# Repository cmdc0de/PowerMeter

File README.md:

# PowerMeter
My take on the power meter inspired by GreatScott

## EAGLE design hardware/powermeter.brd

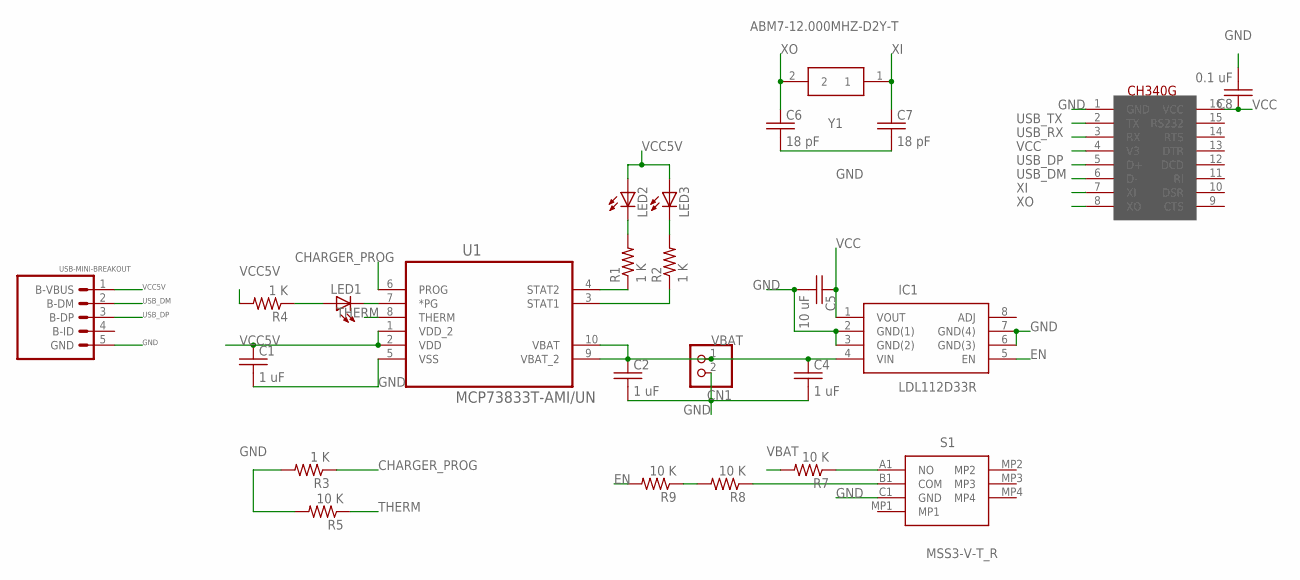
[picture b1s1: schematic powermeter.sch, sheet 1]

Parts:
C1, C2, C4: 1 uF; C0805K
C5: 10 uF; C0805K
C6, C7: 18 pF; C0805K
C8: 0.1 uF; C0805K
CN1: JST_2PIN-THM-RA; JST-PH-2-THM-RA
IC1: LDL112D33R; SOIC127P600X175-8N
LED1, LED2, LED3: LEDXZCFBB53W-8VF-2MA-LED; LEDC1606X95N
R1, R2, R3, R4: 1 K; R0805
R5, R7, R8, R9: 10 K; R0805
S1: MSS3-V-T_R; MSS3VTR
U1: MCP73833T-AMI/UN; SOP50P490X110-10N
U$4: CH340G; SOIC16
USB-MINI-BREAKOUT: USB-MINI-BREAKOUT; 1X05_LONGPADS
Y1: ABM7-12.000MHZ-D2Y-T; ABM7

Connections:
CHARGER_PROG: R3.1, U1.6 (PROG)
EN: IC1.5 (EN), R9.2
GND: C1.2, C2.2, C4.2, C5.2, C6.2, C7.2, C8.2, CN1.2 (1), IC1.2 (GND(1)), IC1.3 (GND(2)), IC1.6 (GND(3)), IC1.7 (GND(4)), R3.2, R5.2, S1.C1 (GND), U1.5 (VSS), U$4.1 (GND), USB-MINI-BREAKOUT.5 (GND); also elsewhere on the board
unnamed: R1.1, U1.4 (STAT2)
unnamed: LED1.2 (C), U1.7 (*PG)
unnamed: LED1.1 (A), R4.1
unnamed: LED3.2 (C), R2.2
unnamed: R2.1, U1.3 (STAT1)
unnamed: LED2.2 (C), R1.2
unnamed: R8.2, R9.1
unnamed: R8.1, S1.B1 (COM)
unnamed: R7.1, S1.A1 (NO)
THERM: R5.1, U1.8 (THERM)
USB_DM: U$4.6 (D-), USB-MINI-BREAKOUT.2 (B-DM)
USB_DP: U$4.5 (D+), USB-MINI-BREAKOUT.3 (B-DP)
USB_RX: U$4.3 (RX); also elsewhere on the board
USB_TX: U$4.2 (TX); also elsewhere on the board
VBAT: C2.1, C4.1, CN1.1 (2), IC1.4 (VIN), R7.2, U1.9 (VBAT_2), U1.10 (VBAT)
VCC: C5.1, C8.1, IC1.1 (VOUT), U$4.4 (V3), U$4.16 (VCC); also elsewhere on the board
VCC5V: C1.1, LED2.1 (A), LED3.1 (A), R4.2, U1.1 (VDD_2), U1.2 (VDD), USB-MINI-BREAKOUT.1 (B-VBUS); also elsewhere on the board
XI: C7.1, U$4.7 (XI), Y1.1
XO: C6.1, U$4.8 (XO), Y1.2

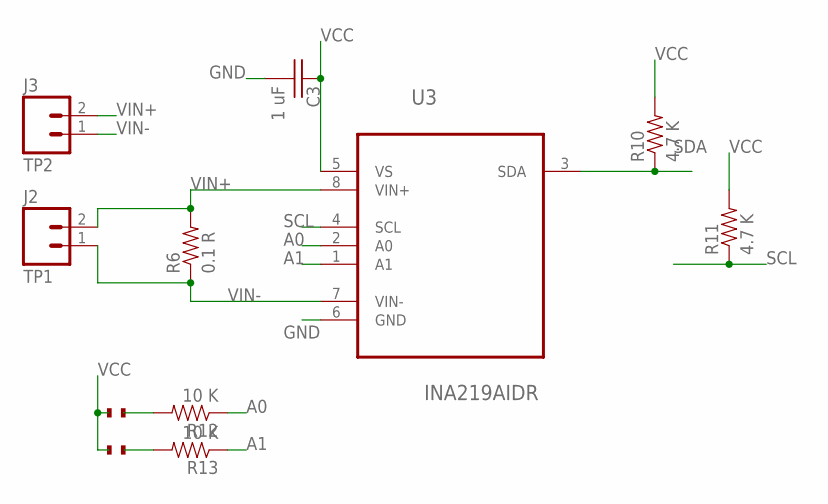
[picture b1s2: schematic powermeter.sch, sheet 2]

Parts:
C3: 1 uF; C0805K
J2: TP1; SCREWTERMINAL-3.5MM-2
J3: TP2; 1X02_LOCK_LONGPADS
R6: 0.1 R; R2010
R10, R11: 4.7 K; R0805
R12, R13: 10 K; R0805
U3: INA219AIDR; SOIC127P600X175-8N
U$1, U$2: SURFACE_MOUNT_JUMP; SURFACE_JUMPER

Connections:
A0: R12.1, U3.2 (A0)
A1: R13.1, U3.1 (A1)
GND: C3.2, U3.6 (GND); also elsewhere on the board
unnamed: R12.2, U$1.2
unnamed: R13.2, U$2.2
SCL: R11.1, U3.4 (SCL); also elsewhere on the board
SDA: R10.1, U3.3 (SDA); also elsewhere on the board
VCC: C3.1, R10.2, R11.2, U3.5 (VS), U$1.1, U$2.1; also elsewhere on the board
VIN+: J2.2, J3.2, R6.2, U3.8 (VIN+)
VIN-: J2.1, J3.1, R6.1, U3.7 (VIN-)

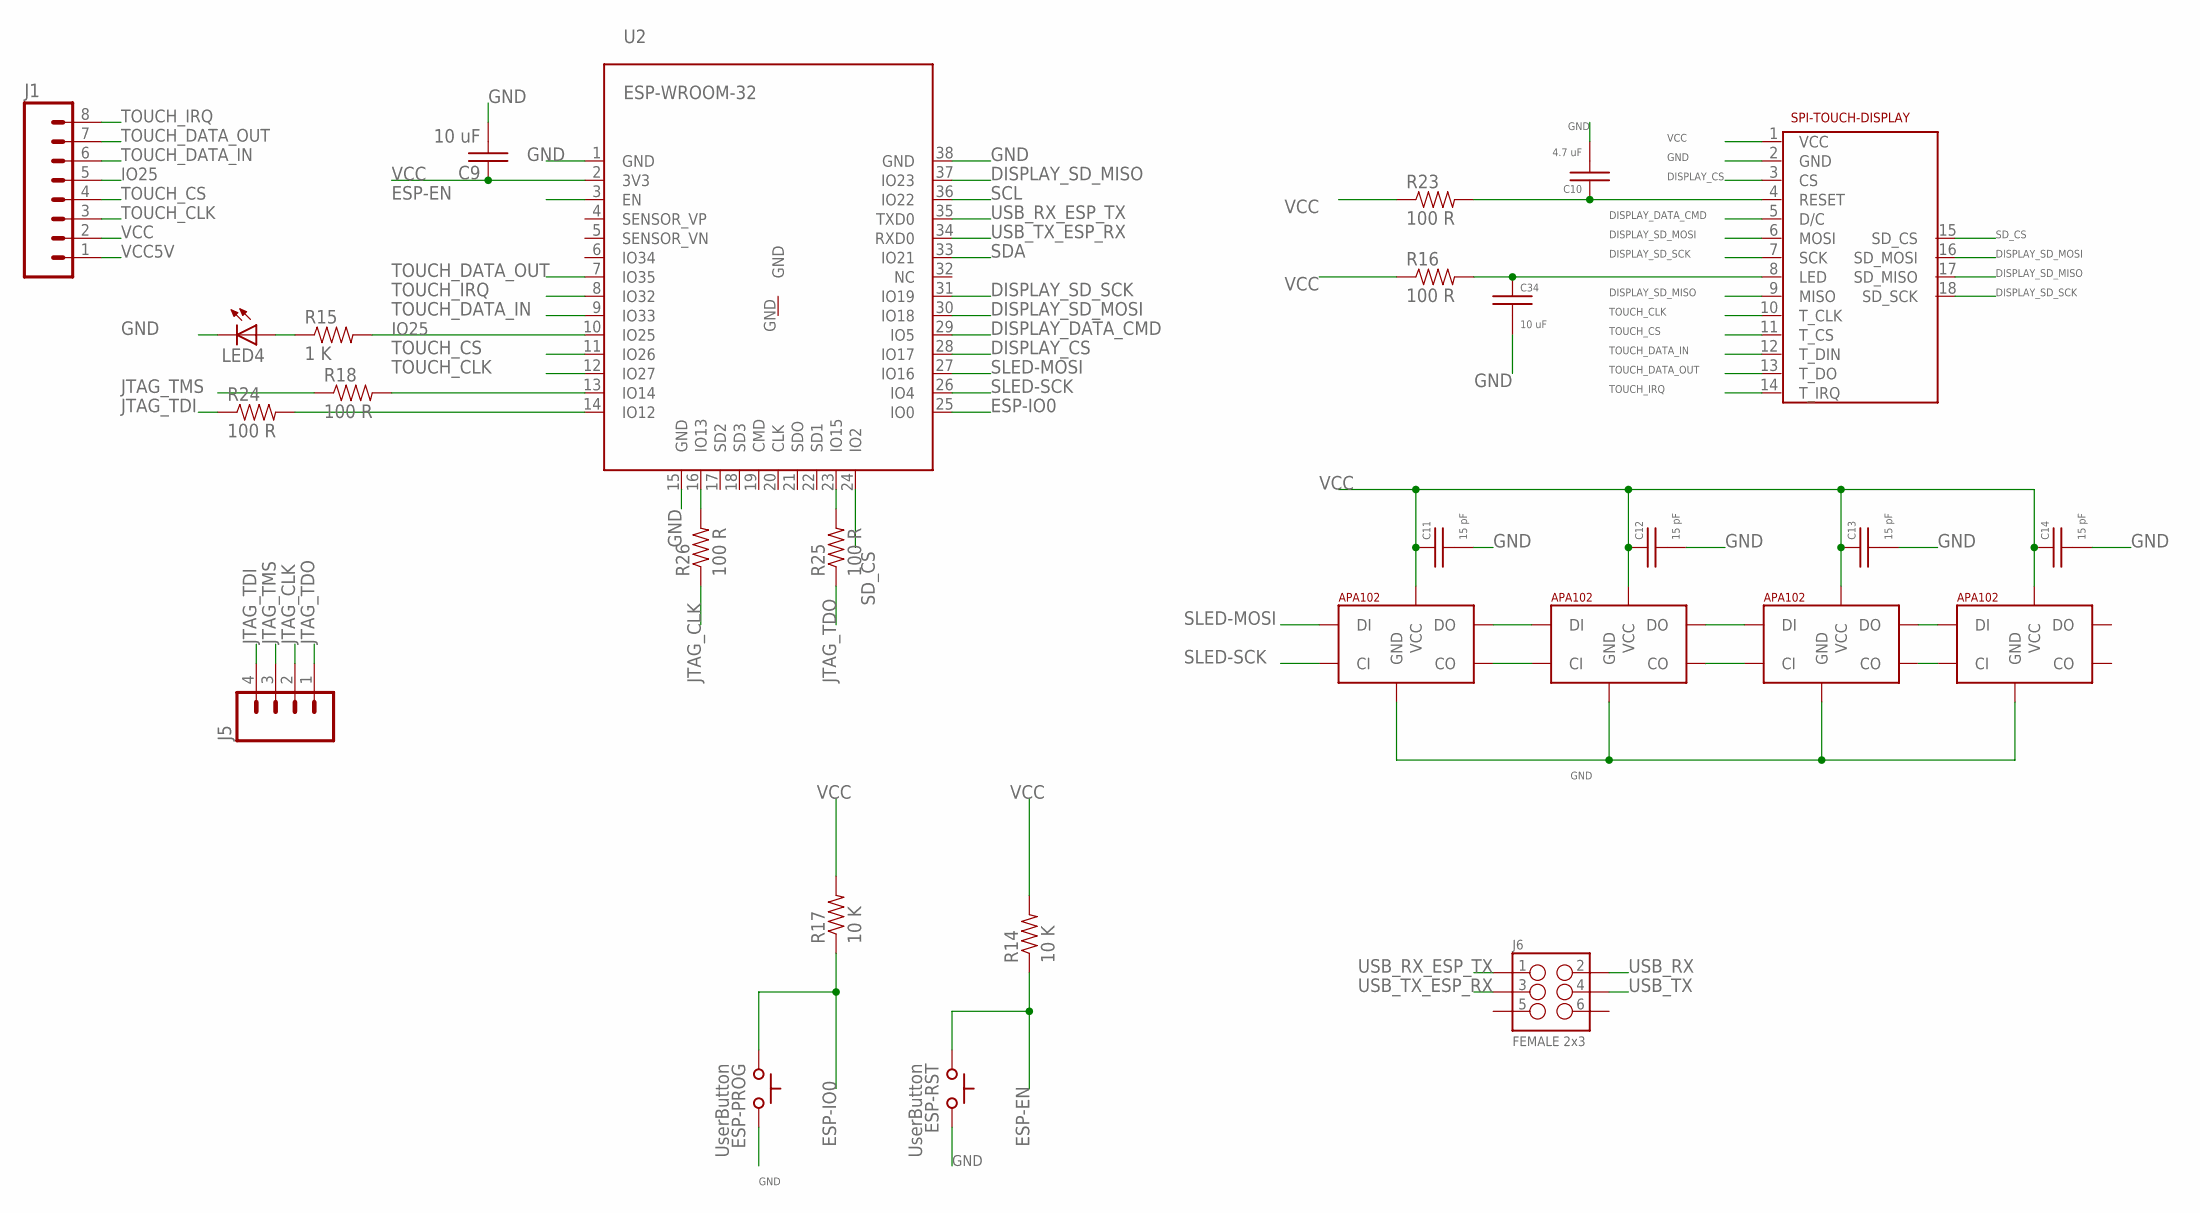
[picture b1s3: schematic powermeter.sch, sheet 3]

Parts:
C9: 10 uF; C0805K
C10: 4.7 uF; C0805
C11, C12, C13, C14: 15 pF; C0805
C34: 10 uF; C0805
ESP-PROG: UserButton; TACTILE-2PIN-NARROW
ESP-RST: UserButton; TACTILE-2PIN-NARROW
J1: M08LONGPADS; 1X08_LONGPADS
J5: M04LONGPADS; 1X04_LONGPADS
J6: FEMALE 2x3; 2X3
LED4: LED1206; LED-1206
R14, R17: 10 K; R0805
R15: 1 K; R0805
R16, R18, R23, R24, R25, R26: 100 R; R0805
U2: ESP-WROOM-32
U$3: 2.4-SPI-TFT-TOUCH-SSD-MODULE
U$5, U$6, U$7, U$8: APA1025050; APA102_5050

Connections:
DISPLAY_BACKLIT: C34.1, R16.2, U$3.8 (LED)
DISPLAY_CS: U2.28 (IO17), U$3.3 (CS)
DISPLAY_DATA_CMD: U2.29 (IO5), U$3.5 (D/C)
DISPLAY_RESET: C10.1, R23.2, U$3.4 (RESET)
DISPLAY_SD_MISO: U2.37 (IO23), U$3.9 (MISO), U$3.17 (SD_MISO)
DISPLAY_SD_MOSI: U2.30 (IO18), U$3.6 (MOSI), U$3.16 (SD_MOSI)
DISPLAY_SD_SCK: U2.31 (IO19), U$3.7 (SCK), U$3.18 (SD_SCK)
ESP-EN: ESP-RST.P$2 (C), R14.1, U2.3 (EN)
ESP-IO0: ESP-PROG.P$2 (C), R17.1, U2.25 (IO0)
GND: C9.2, C10.2, C11.2, C12.2, C13.2, C14.2, C34.2, ESP-PROG.P$1 (A), ESP-RST.P$1 (A), LED4.C, U2.1 (GND), U2.15 (GND), U2.38 (GND), U$3.2 (GND), U$5.6 (GND), U$6.6 (GND), U$7.6 (GND), U$8.6 (GND); also elsewhere on the board
IO25: J1.5, R15.2, U2.10 (IO25)
JTAG_CLK: J5.2, R26.1
JTAG_TDI: J5.4, R24.1
JTAG_TDO: J5.1, R25.1
JTAG_TMS: J5.3, R18.1
unnamed: R24.2, U2.14 (IO12)
unnamed: R26.2, U2.16 (IO13)
unnamed: LED4.A, R15.1
unnamed: U$5.2 (CO), U$6.5 (CI)
unnamed: R18.2, U2.13 (IO14)
unnamed: R25.2, U2.23 (IO15)
unnamed: U$5.3 (DO), U$6.4 (DI)
unnamed: U$6.3 (DO), U$7.4 (DI)
unnamed: U$6.2 (CO), U$7.5 (CI)
unnamed: U$7.2 (CO), U$8.5 (CI)
unnamed: U$7.3 (DO), U$8.4 (DI)
SCL: U2.36 (IO22); also elsewhere on the board
SDA: U2.33 (IO21); also elsewhere on the board
SD_CS: U2.24 (IO2), U$3.15 (SD_CS)
SLED-MOSI: U2.27 (IO16), U$5.4 (DI)
SLED-SCK: U2.26 (IO4), U$5.5 (CI)
TOUCH_CLK: J1.3, U2.12 (IO27), U$3.10 (T_CLK)
TOUCH_CS: J1.4, U2.11 (IO26), U$3.11 (T_CS)
TOUCH_DATA_IN: J1.6, U2.9 (IO33), U$3.12 (T_DIN)
TOUCH_DATA_OUT: J1.7, U2.7 (IO35), U$3.13 (T_DO)
TOUCH_IRQ: J1.8, U2.8 (IO32), U$3.14 (T_IRQ)
USB_RX: J6.2; also elsewhere on the board
USB_RX_ESP_TX: J6.1, U2.35 (TXD0)
USB_TX: J6.4; also elsewhere on the board
USB_TX_ESP_RX: J6.3, U2.34 (RXD0)
VCC: C9.1, C11.1, C12.1, C13.1, C14.1, J1.2, R14.2, R16.1, R17.2, R23.1, U2.2 (3V3), U$3.1 (VCC), U$5.1 (VCC), U$6.1 (VCC), U$7.1 (VCC), U$8.1 (VCC); also elsewhere on the board
VCC5V: J1.1; also elsewhere on the board

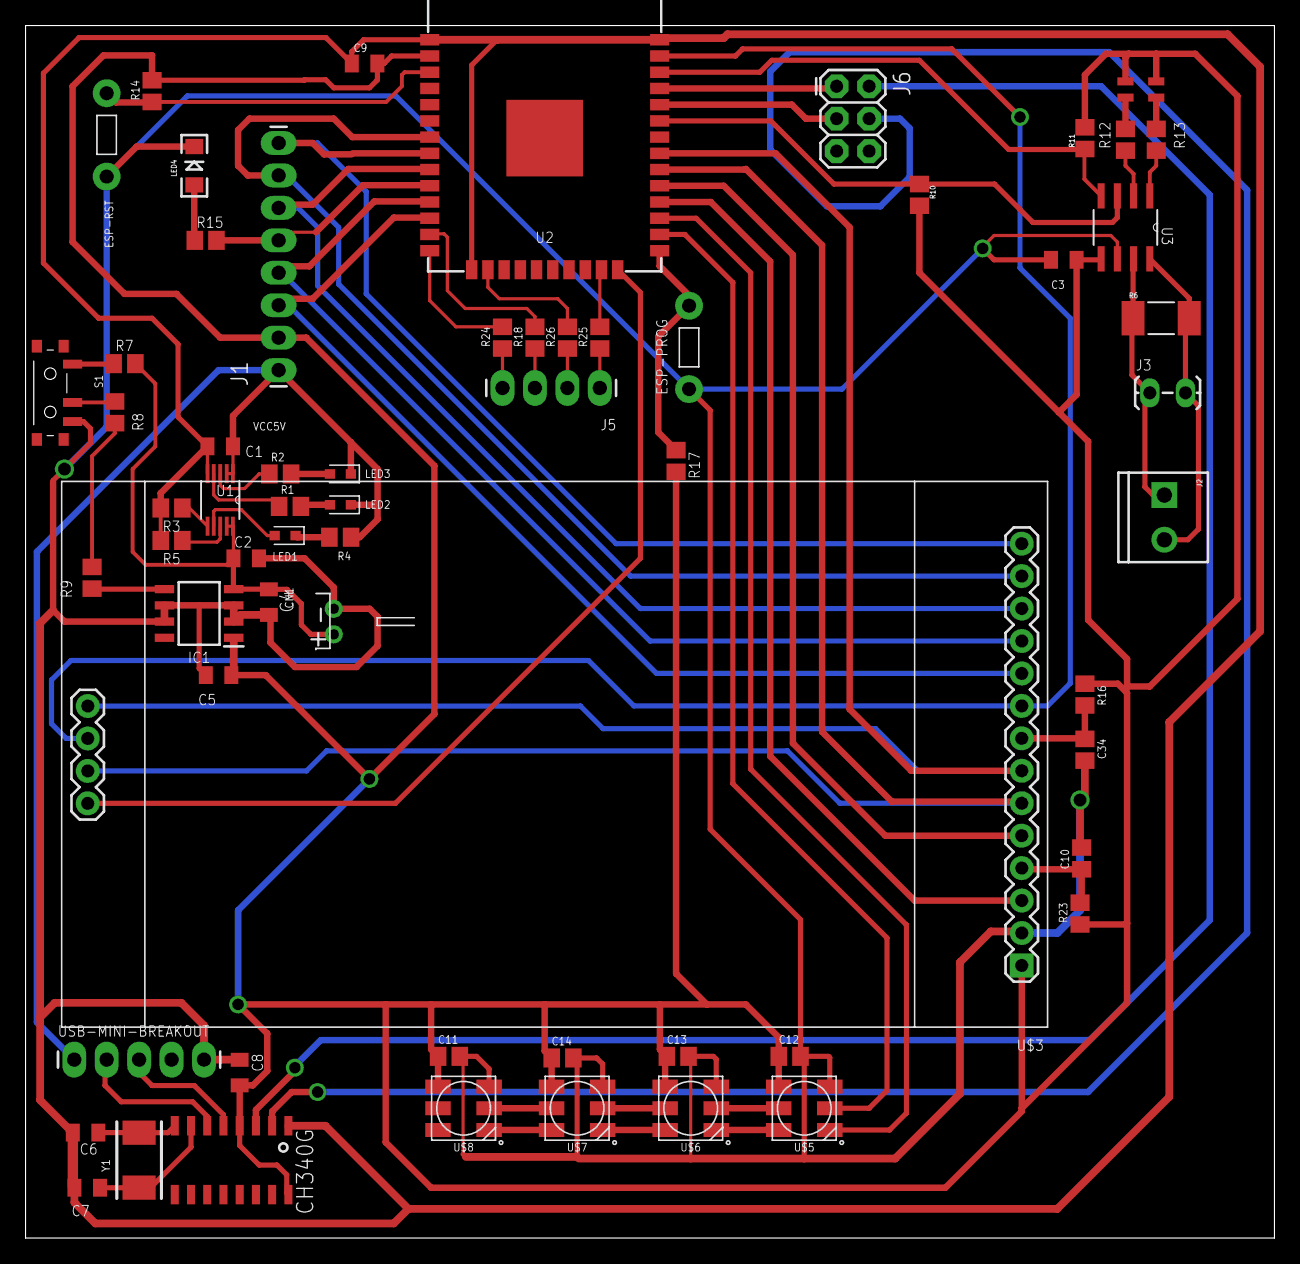
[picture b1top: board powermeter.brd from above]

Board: 2 copper layers, 97.8 x 94.9 mm, 64 parts (0 on the bottom side), 65 nets.

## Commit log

2020-06-01 initial power meter files
2020-06-02 updated gnd plane
2020-06-02 more ground plane work
2020-06-05 no more gnd planes easier to mill
2020-07-12 build env
